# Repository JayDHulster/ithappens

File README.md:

Te bekijken:

* https://github.com/smart-sensor-devices-ab/get_realtime_data_bleuio
* https://chipwired.com/collect-data-with-raspberry-pi/

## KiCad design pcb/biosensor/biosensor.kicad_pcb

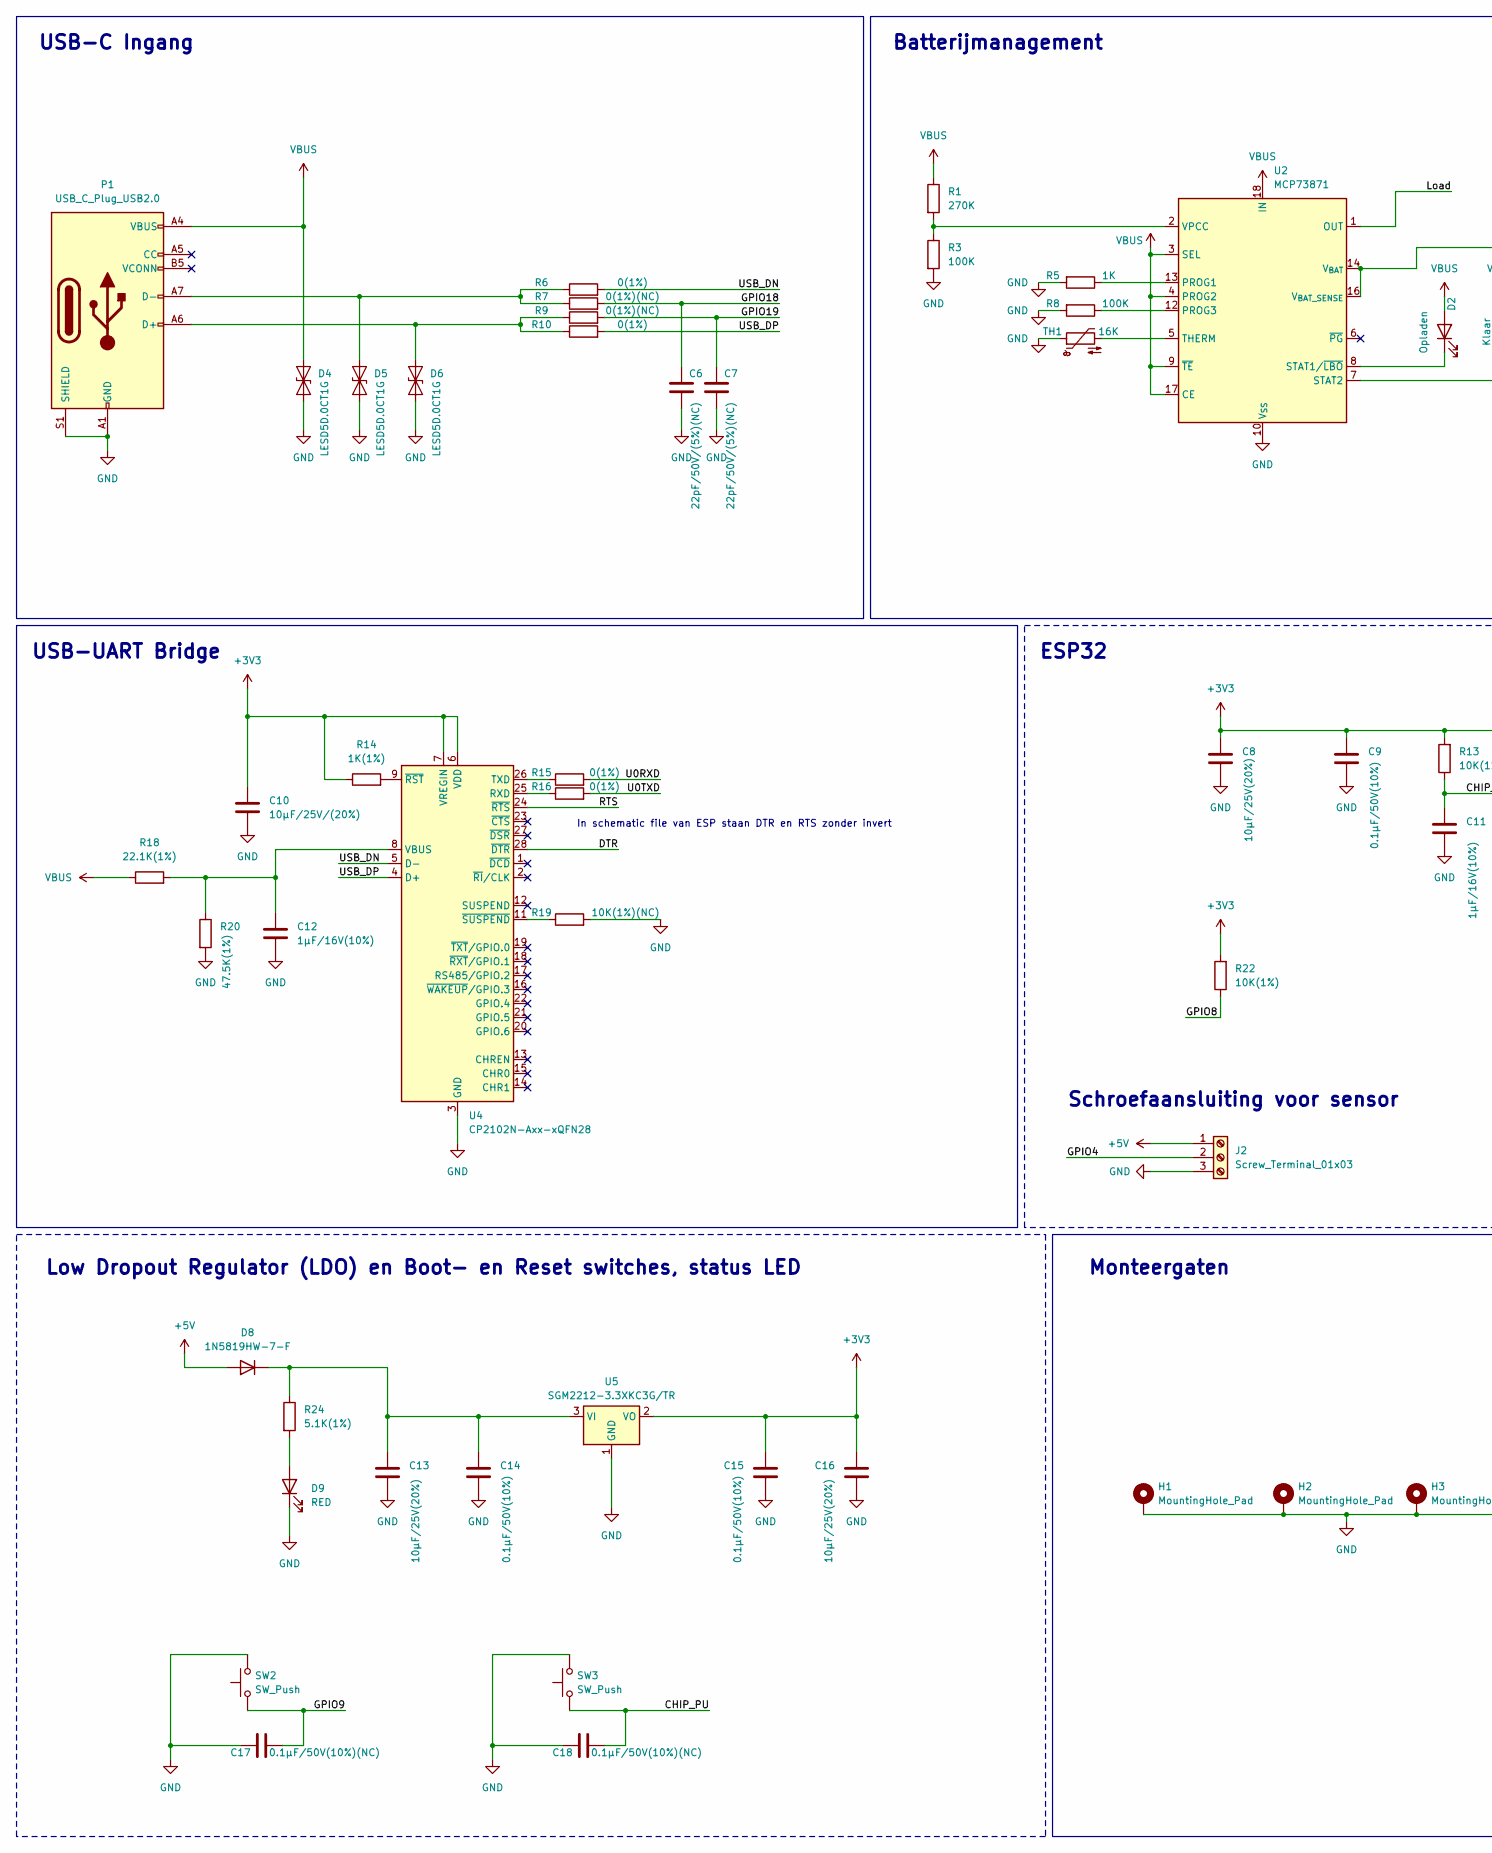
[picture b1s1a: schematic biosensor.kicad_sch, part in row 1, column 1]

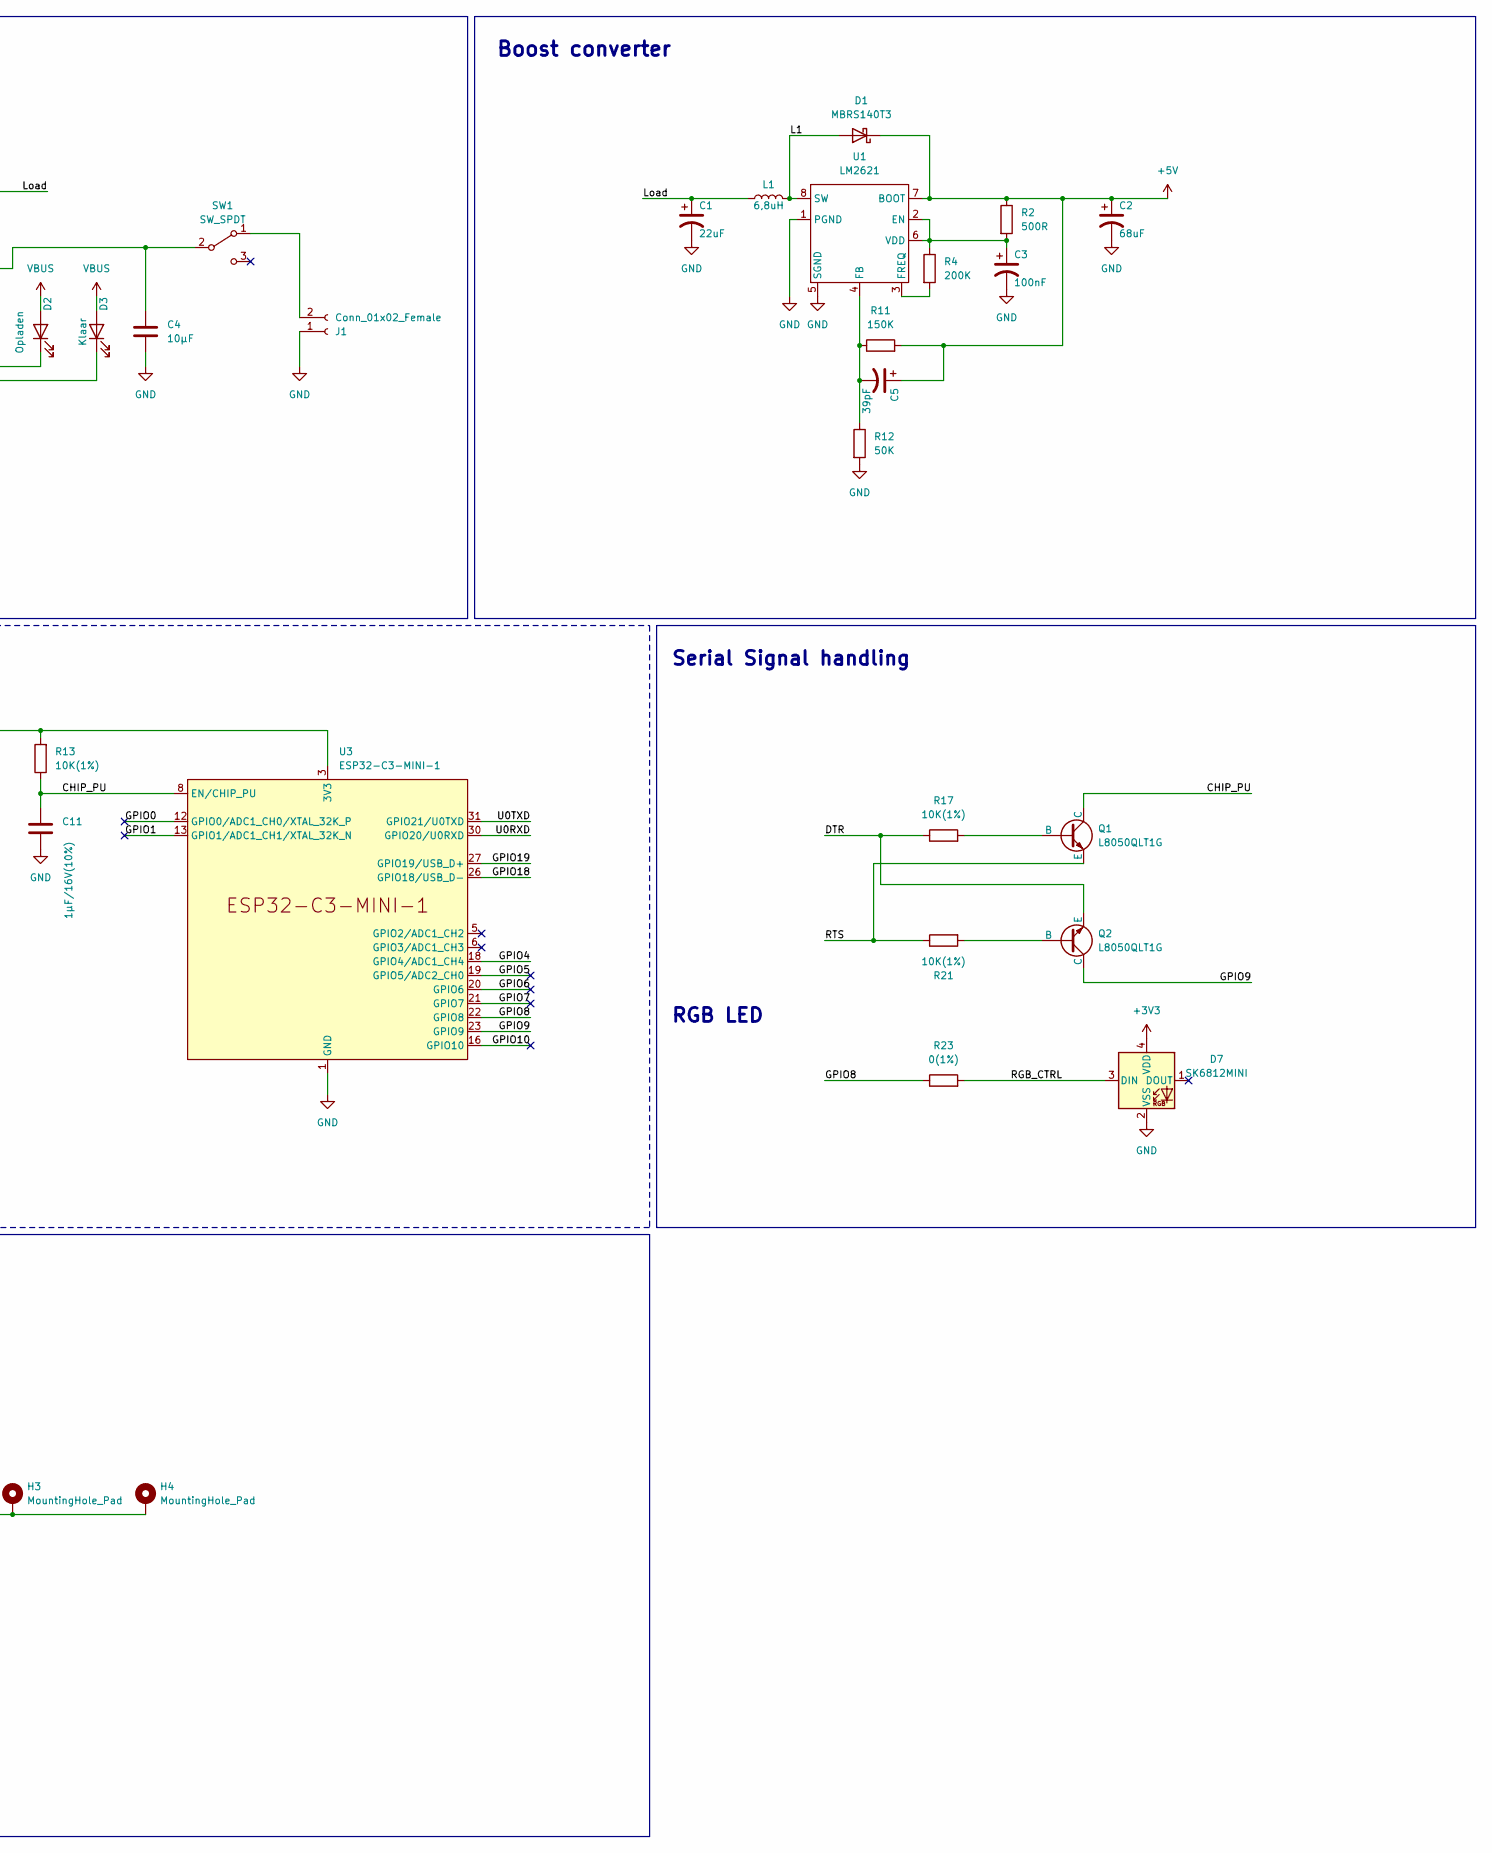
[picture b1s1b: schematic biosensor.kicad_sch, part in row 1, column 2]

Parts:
C1: 22uF; CAP_595D-B_VSS
C2: 68uF; CAP_595D-C_VSS
C3: 100nF; C_0603_1608Metric_Pad1.08x0.95mm_HandSolder
C4: 10µF; C_0603_1608Metric_Pad1.08x0.95mm_HandSolder
C5: 39pF; C_0603_1608Metric_Pad1.08x0.95mm_HandSolder
C6, C7: 22pF/50V/(5%)(NC); C_0603_1608Metric_Pad1.08x0.95mm_HandSolder
C8, C13, C16: 10µF/25V(20%); C_0603_1608Metric_Pad1.08x0.95mm_HandSolder
C9, C14, C15: 0.1µF/50V(10%); C_0603_1608Metric_Pad1.08x0.95mm_HandSolder
C10: 10µF/25V/(20%); C_0603_1608Metric_Pad1.08x0.95mm_HandSolder
C11, C12: 1µF/16V(10%); C_0603_1608Metric_Pad1.08x0.95mm_HandSolder
C17, C18: 0.1µF/50V(10%)(NC); C_0603_1608Metric_Pad1.08x0.95mm_HandSolder
D1: MBRS140T3; D_SMB_Handsoldering
D2: Opladen; LED_0805_2012Metric_Pad1.15x1.40mm_HandSolder
D3: Klaar; LED_0805_2012Metric_Pad1.15x1.40mm_HandSolder
D4, D5, D6: LESD5D.0CT1G; D_SOD-523
D7: SK6812MINI; LED_SK6812MINI_PLCC4_3.5x3.5mm_P1.75mm
D8: 1N5819HW-7-F; D_SOD-123
D9: RED; LED_0805_2012Metric_Pad1.15x1.40mm_HandSolder
H1, H2, H3, H4: MountingHole_Pad; MountingHole_2.7mm_Pad_Via
J1: Conn_01x02_Female; JST_PH_S2B-PH-K_1x02_P2.00mm_Horizontal
J2: Screw_Terminal_01x03; TerminalBlock_bornier-3_P5.08mm
L1: 6,8uH; LPS4018223MRC
P1: USB_C_Plug_USB2.0; USB_C_Receptacle_HRO_TYPE-C-31-M-12
Q1, Q2: L8050QLT1G; SOT-23
R1: 270K; R_0603_1608Metric_Pad0.98x0.95mm_HandSolder
R2: 500R; R_0603_1608Metric
R3, R8: 100K; R_0603_1608Metric_Pad0.98x0.95mm_HandSolder
R4: 200K; R_0603_1608Metric
R5: 1K; R_0603_1608Metric_Pad0.98x0.95mm_HandSolder
R6, R10, R15, R16, R23: 0(1%); R_0603_1608Metric_Pad0.98x0.95mm_HandSolder
R7, R9: 0(1%)(NC); R_0603_1608Metric_Pad0.98x0.95mm_HandSolder
R11: 150K; R_0603_1608Metric_Pad0.98x0.95mm_HandSolder
R12: 50K; R_0603_1608Metric_Pad0.98x0.95mm_HandSolder
R13, R17, R21, R22: 10K(1%); R_0603_1608Metric_Pad0.98x0.95mm_HandSolder
R14: 1K(1%); R_0603_1608Metric_Pad0.98x0.95mm_HandSolder
R18: 22.1K(1%); R_0603_1608Metric_Pad0.98x0.95mm_HandSolder
R19: 10K(1%)(NC); R_0603_1608Metric_Pad0.98x0.95mm_HandSolder
R20: 47.5K(1%); R_0603_1608Metric_Pad0.98x0.95mm_HandSolder
R24: 5.1K(1%); R_0603_1608Metric_Pad0.98x0.95mm_HandSolder
SW1: SW_SPDT; SW_Slide_1P2T_CK_OS102011MS2Q
SW2, SW3: SW_Push; SW_PUSH_6mm
TH1: 16K; R_0603_1608Metric_Pad0.98x0.95mm_HandSolder
U1: LM2621; VSSOP-8_3.0x3.0mm_P0.65mm
U2: MCP73871; QFN-20-1EP_4x4mm_P0.5mm_EP2.5x2.5mm
U3: ESP32-C3-MINI-1
U4: CP2102N-Axx-xQFN28; QFN-28-1EP_5x5mm_P0.5mm_EP3.35x3.35mm
U5: SGM2212-3.3XKC3G/TR; SOT-223-3_TabPin2

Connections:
+3V3: C8.1, C9.1, C10.1, C15.1, C16.1, D7.4 (VDD), R13.2, R14.1, R22.2, U3.3 (3V3), U4.6 (VDD), U4.7 (VREGIN), U5.2 (VO)
+5V: C2.1, C5.1, D1.1 (K), D8.2 (A), J2.1, R2.1, R11.2, U1.7 (BOOT)
/CHIP_PU: C11.1, C18.2, Q1.1 (C), R13.1, SW3.1, U3.8 (EN/CHIP_PU)
/DTR: Q2.3 (E), R17.1, U4.28 (~DTR)
/GPIO0: U3.12 (GPIO0/ADC1_CH0/XTAL_32K_P)
/GPIO1: U3.13 (GPIO1/ADC1_CH1/XTAL_32K_N)
/GPIO4: J2.2, U3.18 (GPIO4/ADC1_CH4)
/GPIO5: U3.19 (GPIO5/ADC2_CH0)
/GPIO6: U3.20 (GPIO6)
/GPIO7: U3.21 (GPIO7)
/GPIO8: R22.1, R23.1, U3.22 (GPIO8)
/GPIO9: C17.2, Q2.1 (C), SW2.1, U3.23 (GPIO9)
/GPIO10: U3.16 (GPIO10)
/GPIO18: C6.1, R7.2, U3.26 (GPIO18/USB_D-)
/GPIO19: C7.1, R9.2, U3.27 (GPIO19/USB_D+)
/L1: D1.2 (A), L1.2, U1.8 (SW)
/Load: C1.1, L1.1, U2.1 (OUT), U2.20 (OUT)
/RGB_CTRL: D7.3 (DIN), R23.2
/RTS: Q1.3 (E), R21.1, U4.24 (~RTS)
/U0RXD: R15.2, U3.30 (GPIO20/U0RXD)
/U0TXD: R16.2, U3.31 (GPIO21/U0TXD)
/USB_DN: R6.2, U4.5 (D-)
/USB_DP: R10.2, U4.4 (D+)
GND: C1.2, C2.2, C3.2, C4.2, C6.2, C7.2, C8.2, C9.2, C10.2, C11.2, C12.2, C13.2, C14.2, C15.2, C16.2, C17.1, C18.1, D4.1 (A1), D5.1 (A1), D6.1 (A1), D7.2 (VSS), D9.1 (K), H1.1, H2.1, H3.1, H4.1, J1.1, J2.3, P1.A1 (GND), P1.A12 (GND), P1.B1 (GND), P1.B12 (GND), P1.S1 (SHIELD), R3.2, R5.2, R8.2, R12.2, R19.2, R20.2, SW2.2, SW3.2, TH1.1, U1.1 (PGND), U1.5 (SGND), U2.10 (V_{SS}), U2.11 (V_{SS}), U2.21 (V_{SS}), U3.1 (GND), U3.2 (GND), U3.11 (GND), U3.14 (GND), U3.36 (GND), U3.37 (GND), U3.38 (GND), U3.39 (GND), U3.40 (GND), U3.41 (GND), U3.42 (GND), U3.43 (GND), U3.44 (GND), U3.45 (GND), U3.46 (GND), U3.47 (GND), U3.48 (GND), U3.49 (GND), U3.50 (GND), U3.51 (GND), U3.52 (GND), U3.53 (GND), U4.3 (GND), U4.29 (GND), U5.1 (GND)
unnamed: D2.1 (K), U2.8 (STAT1/~LBO)
unnamed: D3.1 (K), U2.7 (STAT2)
unnamed: D5.2 (A2), P1.A7 (D-), R6.1, R7.1
unnamed: D6.2 (A2), P1.A6 (D+), R9.1, R10.1
unnamed: C13.1, C14.1, D8.1 (K), R24.1, U5.3 (VI)
unnamed: D9.2 (A), R24.2
unnamed: J1.2, SW1.1 (A)
unnamed: Q1.2 (B), R17.2
unnamed: Q2.2 (B), R21.2
unnamed: C4.1, SW1.2 (B), U2.14 (V_{BAT}), U2.15 (V_{BAT}), U2.16 (V_{BAT_SENSE})
unnamed: C3.1, R2.2, R4.1, U1.2 (EN), U1.6 (VDD)
unnamed: C5.2, R11.1, R12.1, U1.4 (FB)
unnamed: R4.2, U1.3 (FREQ)
unnamed: R5.1, U2.13 (PROG1)
unnamed: R8.1, U2.12 (PROG3)
unnamed: TH1.2, U2.5 (THERM)
unnamed: R1.2, R3.1, U2.2 (VPCC)
unnamed: R16.1, U4.25 (RXD)
unnamed: R15.1, U4.26 (TXD)
unnamed: C12.1, R18.2, R20.1, U4.8 (VBUS)
unnamed: R14.2, U4.9 (~RST)
unnamed: R19.1, U4.11 (~SUSPEND)
VBUS: D2.2 (A), D3.2 (A), D4.2 (A2), P1.A4 (VBUS), P1.A9 (VBUS), P1.B4 (VBUS), P1.B9 (VBUS), R1.1, R18.1, U2.3 (SEL), U2.4 (PROG2), U2.9 (~TE), U2.17 (CE), U2.18 (IN), U2.19 (IN)

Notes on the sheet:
Low Dropout Regulator (LDO) en Boot- en Reset switches, status LED
RGB LED
USB-C Ingang
In schematic file van ESP staan DTR en RTS zonder invert
Boost converter
Monteergaten
USB-UART Bridge
Batterijmanagement
Serial Signal handling
Schroefaansluiting voor sensor
ESP32

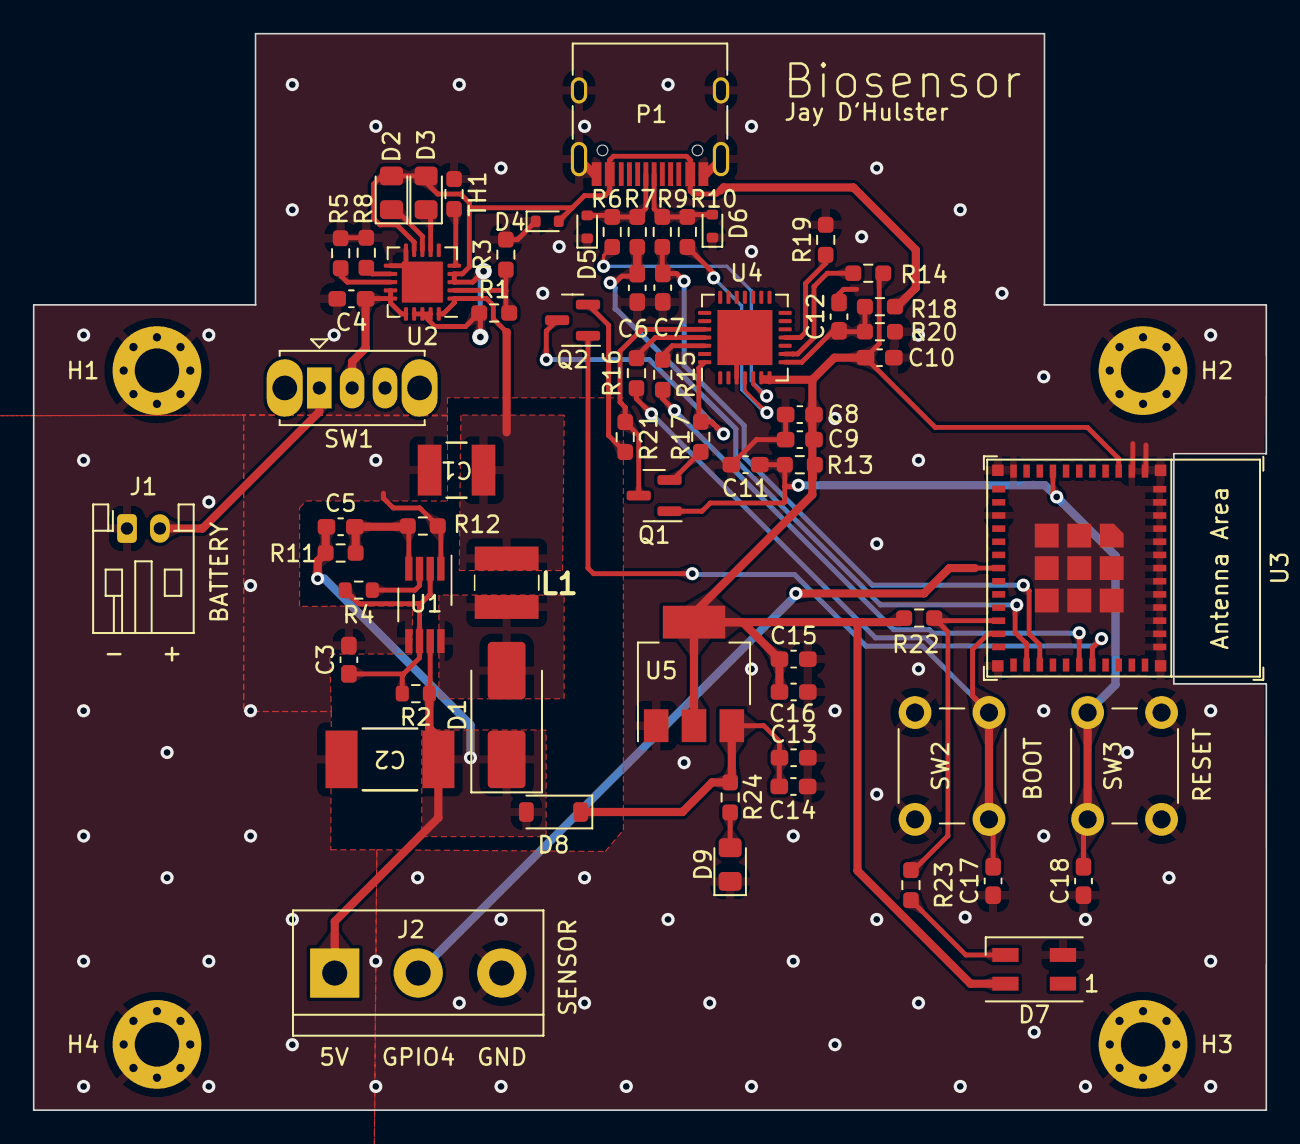
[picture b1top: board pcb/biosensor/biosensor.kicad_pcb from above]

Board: 2 copper layers, 75.0 x 65.5 mm, 70 parts (0 on the bottom side), 41 nets.

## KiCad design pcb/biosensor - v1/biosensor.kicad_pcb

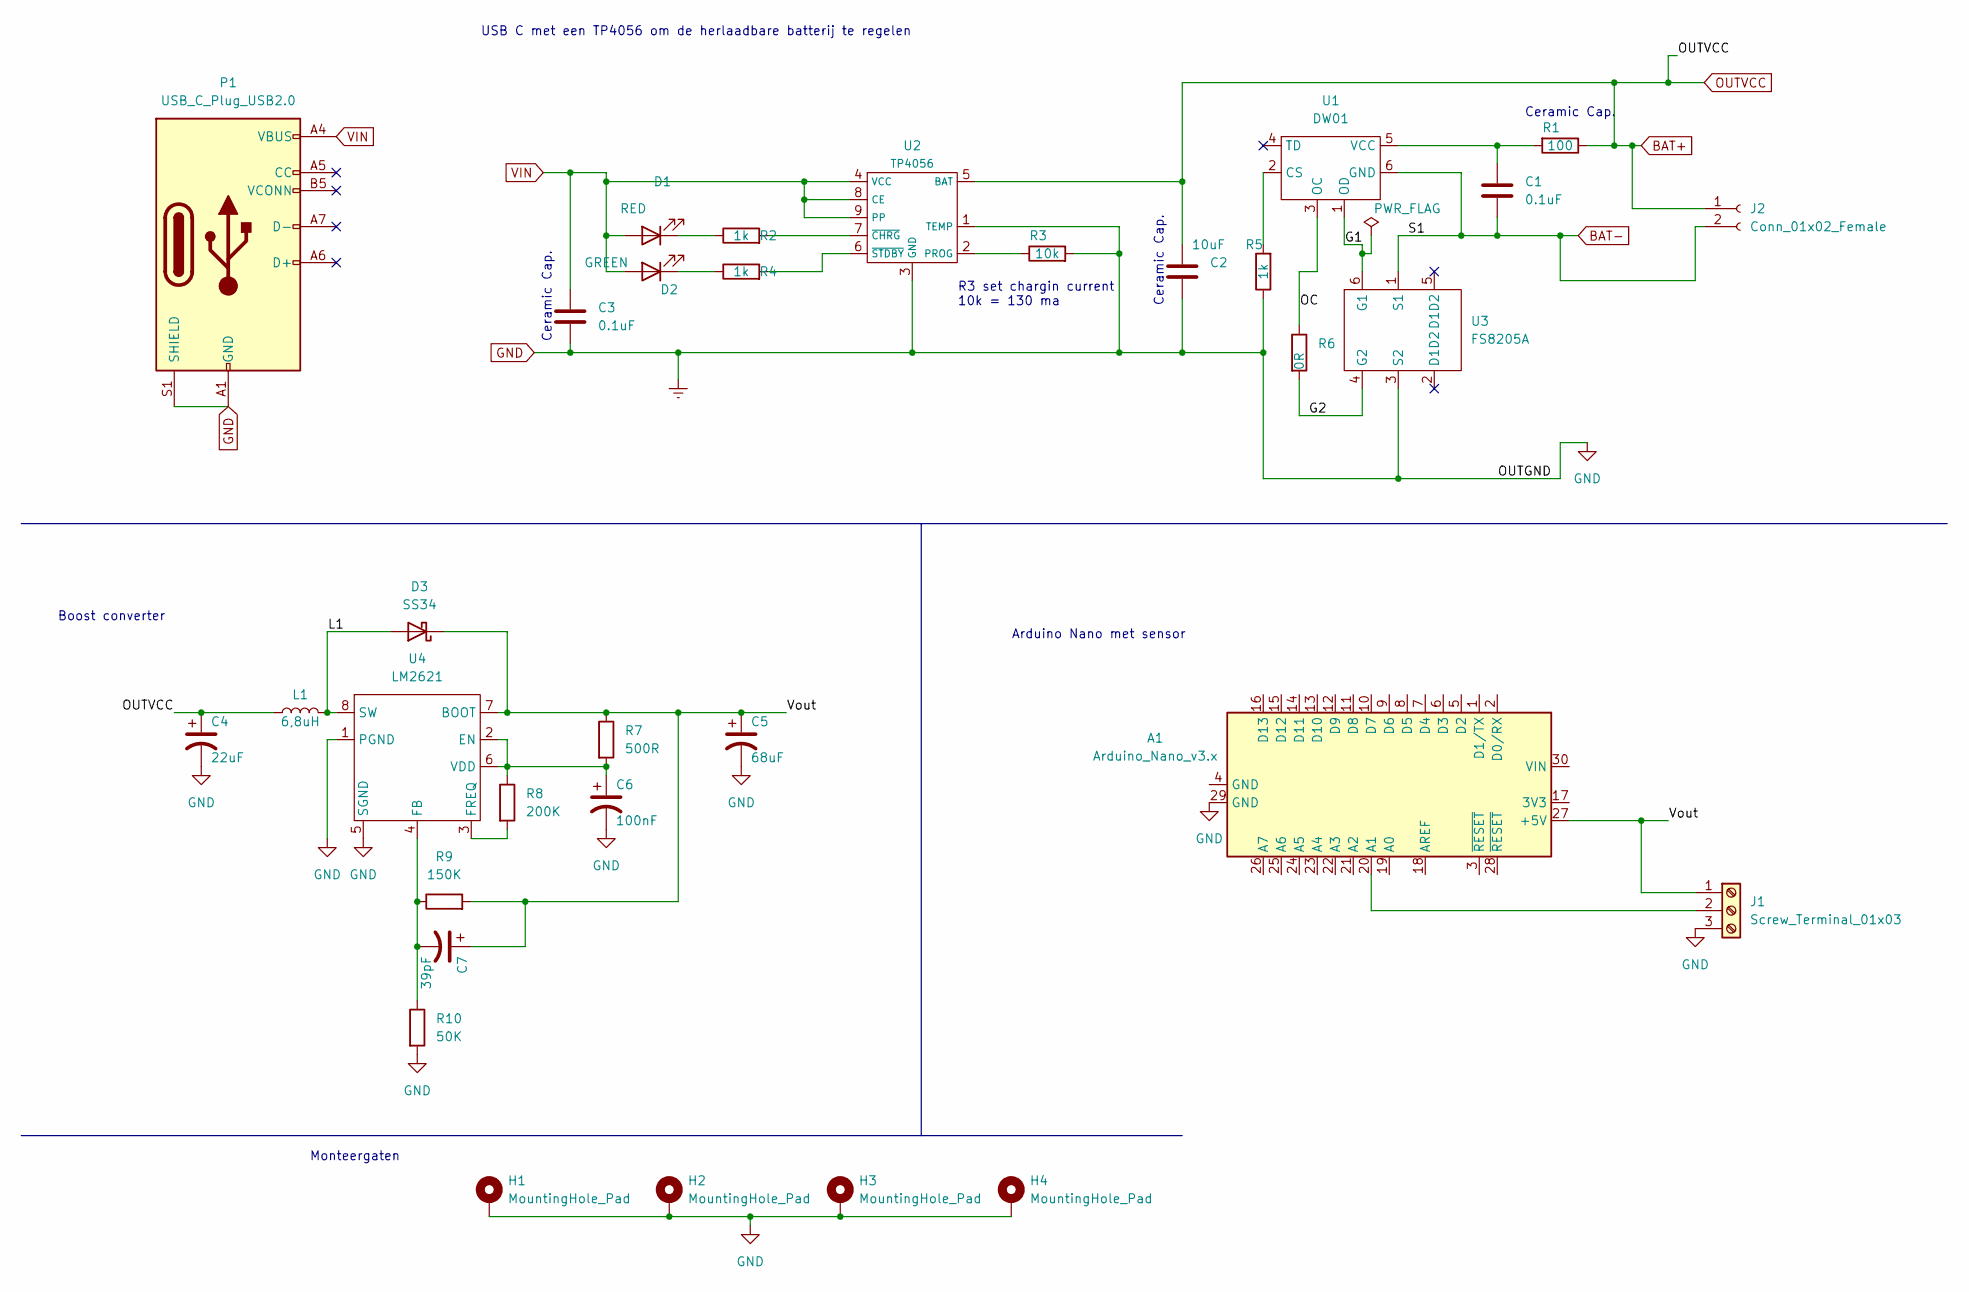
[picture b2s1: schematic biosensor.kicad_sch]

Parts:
A1: Arduino_Nano_v3.x; Arduino_Nano
C1, C3: 0.1uF; C_0805_2012Metric_Pad1.18x1.45mm_HandSolder
C2: 10uF; C_0805_2012Metric_Pad1.18x1.45mm_HandSolder
C4: 22uF; C_2225_5664Metric_Pad1.80x6.60mm_HandSolder
C5: 68uF; C_2225_5664Metric_Pad1.80x6.60mm_HandSolder
C6: 100nF; C_0603_1608Metric_Pad1.08x0.95mm_HandSolder
C7: 39pF; C_0805_2012Metric_Pad1.18x1.45mm_HandSolder
D1: RED; LED_0805_2012Metric_Pad1.15x1.40mm_HandSolder
D2: GREEN; LED_0805_2012Metric_Pad1.15x1.40mm_HandSolder
D3: SS34; D_SMA_Handsoldering
H1, H2, H3, H4: MountingHole_Pad; MountingHole_2.7mm_Pad_Via
J1: Screw_Terminal_01x03; TerminalBlock_bornier-3_P5.08mm
J2: Conn_01x02_Female; Molex_PicoBlade_53048-0210_1x02_P1.25mm_Horizontal
L1: 6,8uH; L_12x12mm_H8mm
P1: USB_C_Plug_USB2.0; USB_C_Receptacle_HRO_TYPE-C-31-M-12
R1: 100; R_0805_2012Metric_Pad1.20x1.40mm_HandSolder
R2, R4, R5: 1k; R_0603_1608Metric_Pad0.98x0.95mm_HandSolder
R3: 10k; R_0805_2012Metric_Pad1.20x1.40mm_HandSolder
R6: 0R; R_1206_3216Metric_Pad1.30x1.75mm_HandSolder
R7: 500R; R_0603_1608Metric
R8: 200K; R_0603_1608Metric
R9: 150K; R_0805_2012Metric_Pad1.20x1.40mm_HandSolder
R10: 50K; R_0603_1608Metric
U1: DW01; SOT-23-6_Handsoldering
U2: TP4056; SOIC-8-1EP_3.9x4.9mm_P1.27mm_EP2.29x3mm
U3: FS8205A; SOT-23-6_Handsoldering
U4: LM2621; VSSOP-8_3.0x3.0mm_P0.65mm

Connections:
/G1: U1.1 (OD), U3.6 (G1)
/G2: R6.2, U3.4 (G2)
/L1: D3.2 (A), L1.2, U4.8 (SW)
/OC: R6.1, U1.3 (OC)
/Vout: A1.27 (+5V), C5.1, C7.1, D3.1 (K), J1.1, R7.1, R9.2, U4.7 (BOOT)
BAT+: C2.1, C4.1, J2.1, L1.1, R1.1, U2.5 (BAT)
BAT-: C1.2, J2.2, U1.6 (GND), U3.1 (S1)
GND: A1.29 (GND), C2.2, C3.2, C4.2, C5.2, C6.2, H1.1, H2.1, H3.1, H4.1, J1.3, P1.A1 (GND), P1.A12 (GND), P1.B1 (GND), P1.B12 (GND), P1.S1 (SHIELD), R3.2, R5.1, R10.2, U2.1 (TEMP), U2.3 (GND), U3.3 (S2), U4.1 (PGND), U4.5 (SGND)
unnamed: A1.20 (A1), J1.2
unnamed: C1.1, R1.2, U1.5 (VCC)
unnamed: C6.1, R7.2, R8.1, U4.2 (EN), U4.6 (VDD)
unnamed: C7.2, R9.1, R10.1, U4.4 (FB)
unnamed: D1.1 (K), R2.1
unnamed: D2.1 (K), R4.1
unnamed: R2.2, U2.7 (~CHRG)
unnamed: R3.1, U2.2 (PROG)
unnamed: R4.2, U2.6 (~STDBY)
unnamed: R5.2, U1.2 (CS)
unnamed: R8.2, U4.3 (FREQ)
VIN: C3.1, D1.2 (A), D2.2 (A), P1.A4 (VBUS), P1.A9 (VBUS), P1.B4 (VBUS), P1.B9 (VBUS), U2.4 (VCC), U2.8 (CE), U2.9 (PP)

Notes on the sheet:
R3 set chargin current 10k = 130 ma
Boost converter
Arduino Nano met sensor
Ceramic Cap.
Monteergaten
USB C met een TP4056 om de herlaadbare batterij te regelen

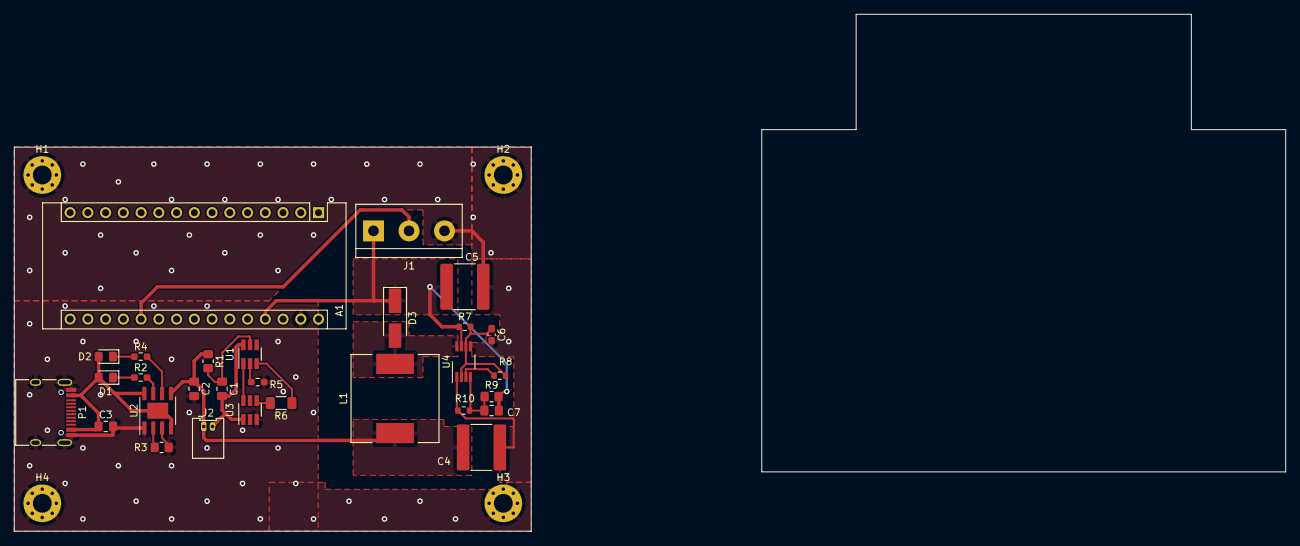
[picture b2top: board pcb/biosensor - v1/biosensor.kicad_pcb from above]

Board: 2 copper layers, 182.0 x 74.0 mm, 33 parts (0 on the bottom side), 20 nets.

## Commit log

2023-03-24 pcb files
2023-03-24 working http but we need mqtt
2023-06-01 before esp change
2023-06-04 massive update to pcb
2023-06-07 final update?
2023-06-10 docker
2023-06-10 save
